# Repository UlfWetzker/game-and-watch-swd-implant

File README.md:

# Game & Watch SWD-Implant

A small [DAP-Link](https://github.com/ARMmbed/DAPLink) SWD programmer/debugger that fits insight a Nintendo® Game & Watch™ 2020.

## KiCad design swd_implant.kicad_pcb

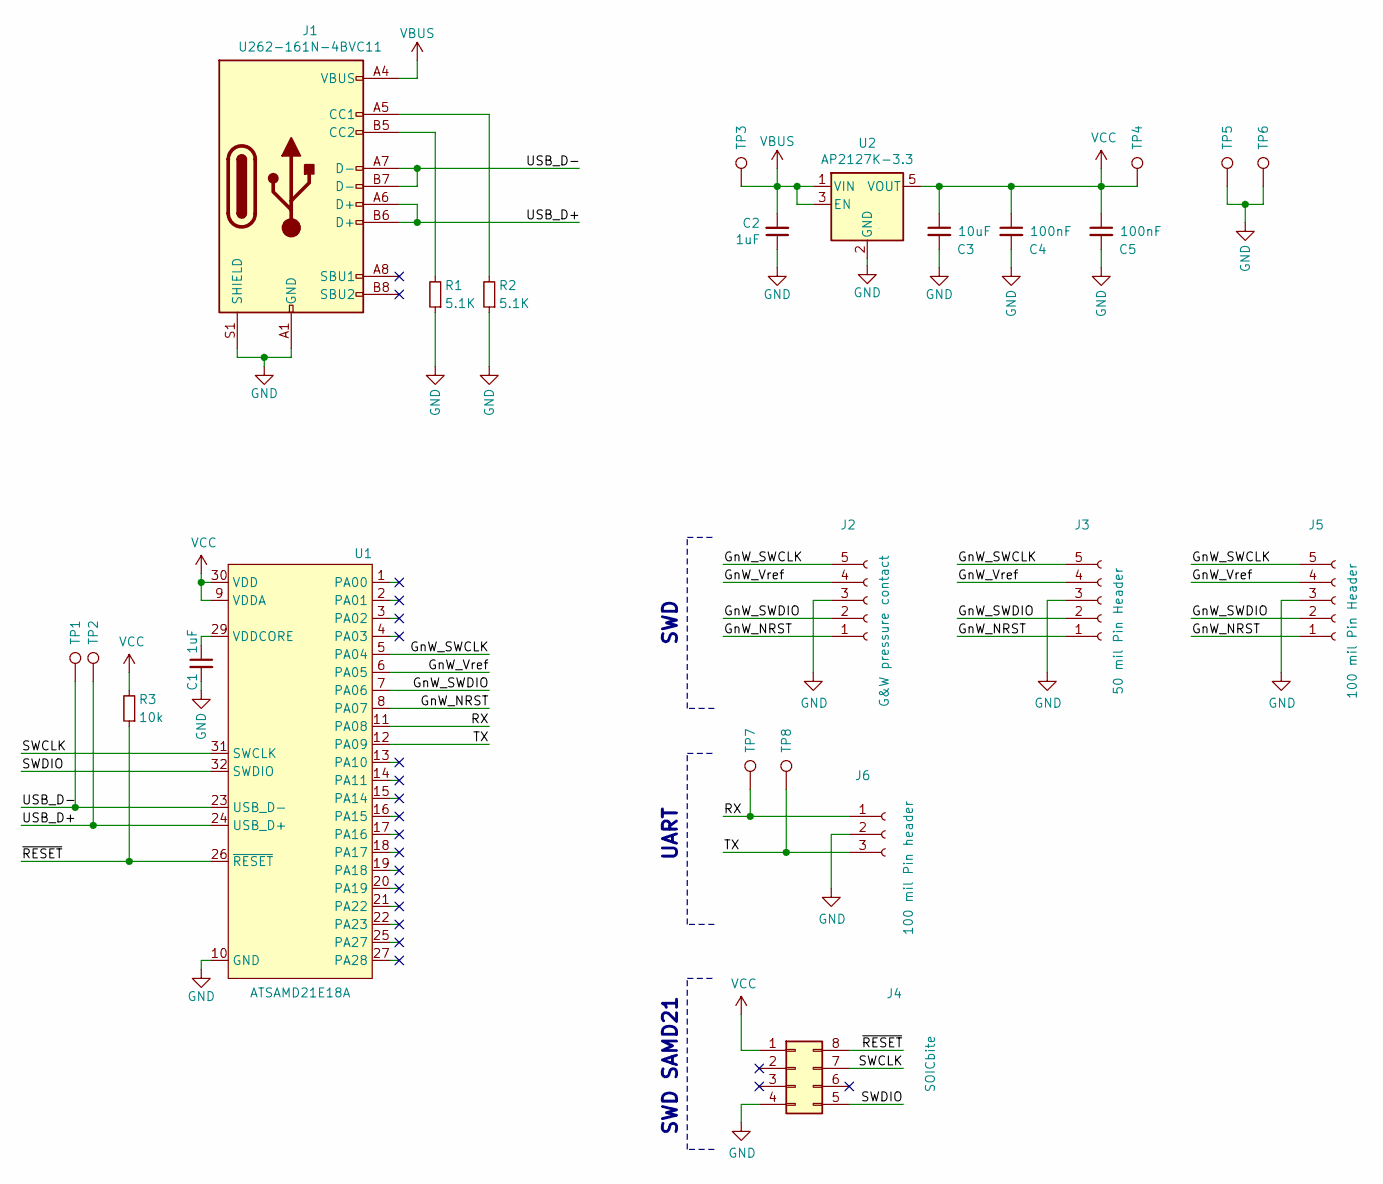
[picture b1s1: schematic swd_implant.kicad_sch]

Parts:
C1, C2: 1uF; C_0402_1005Metric; MFR.Part # CL05A105KA5NQNC; LCSC Part # C52923
C3: 10uF; C_0402_1005Metric; MFR.Part # CL05A106MQ5NUNC; LCSC Part # C15525
C4, C5: 100nF; C_0402_1005Metric; MFR.Part # CL05B104KO5NNNC; LCSC Part # C1525
J1: U262-161N-4BVC11; USB_C_Receptacle_XKB_U262-16XN-4BVC11; Mfr.Part # U262-161N-4BVC11; LCSC Part # C319148
J2: G&W pressure contact; GnW_SWD
J3: 50 mil Pin Header; PinHeader_1x05_P1.27mm_Vertical
J4: SOICbite; SOIC_clipProgSmall
J5: 100 mil Pin Header; PinHeader_1x05_P2.45mm_edge
J6: 100 mil Pin header; PinHeader_1x03_P2.45mm_edge
R1, R2: 5.1K; R_0402_1005Metric; MFR.Part # 0402WGF5101TCE; LCSC Part # C25905
R3: 10k; R_0402_1005Metric; MFR.Part # 0402WGJ0103TCE; LCSC Part # C25531
TP1, TP3, TP4, TP5, TP6, TP7, TP8: TP_USB_D+; TestPoint_Pad_D1.0mm
TP2: TP_USB_D-; TestPoint_Pad_D1.0mm
U1: ATSAMD21E18A; QFN-32-1EP_5x5mm_P0.5mm_EP3.6x3.6mm; MFR.Part # ATSAMD21E18A-MU; LCSC Part # C220692
U2: AP2127K-3.3; SOT-23-5; MFR.Part # AP2127K-3.3TRG1; LCSC Part # C156285

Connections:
/GnW_NRST: J2.1, J3.1, J5.1, U1.8 (PA07)
/GnW_SWCLK: J2.5, J3.5, J5.5, U1.5 (PA04)
/GnW_SWDIO: J2.2, J3.2, J5.2, U1.7 (PA06)
/GnW_Vref: J2.4, J3.4, J5.4, U1.6 (PA05)
/RX: J6.1, TP7.1, U1.11 (PA08)
/SWCLK: J4.7, U1.31 (SWCLK)
/SWDIO: J4.5, U1.32 (SWDIO)
/TX: J6.3, TP8.1, U1.12 (PA09)
/USB_D+: J1.A6 (D+), J1.B6 (D+), TP2.1, U1.24 (USB_D+)
/USB_D-: J1.A7 (D-), J1.B7 (D-), TP1.1, U1.23 (USB_D-)
/~RESET~: J4.8, R3.1, U1.26 (~RESET~)
GND: C1.2, C2.1, C3.2, C4.2, C5.2, J1.A1 (GND), J1.A12 (GND), J1.B1 (GND), J1.B12 (GND), J1.S1 (SHIELD), J2.3, J2.6, J2.7, J3.3, J4.4, J5.3, J6.2, R1.1, R2.1, TP5.1, TP6.1, U1.10 (GND), U1.28 (GND), U1.33, U2.2 (GND); also elsewhere on the board
unnamed: C1.1, U1.29 (VDDCORE)
unnamed: J1.A5 (CC1), R2.2
unnamed: J1.B5 (CC2), R1.2
VBUS: C2.2, J1.A4 (VBUS), J1.A9 (VBUS), J1.B4 (VBUS), J1.B9 (VBUS), TP3.1, U2.1 (VIN), U2.3 (EN)
VCC: C3.1, C4.1, C5.1, J4.1, R3.2, TP4.1, U1.9 (VDDA), U1.30 (VDD), U2.5 (VOUT)
no_connect_18: J1.A8 (SBU1)
no_connect_19: J1.B8 (SBU2)
no_connect_20: J4.2
no_connect_21: J4.3
no_connect_22: J4.6
no_connect_23: U1.1 (PA00)
no_connect_24: U1.13 (PA10)
no_connect_25: U1.14 (PA11)
no_connect_26: U1.15 (PA14)
no_connect_27: U1.16 (PA15)
no_connect_28: U1.17 (PA16)
no_connect_29: U1.18 (PA17)
no_connect_30: U1.19 (PA18)
no_connect_31: U1.2 (PA01)
no_connect_32: U1.20 (PA19)
no_connect_33: U1.21 (PA22)
no_connect_34: U1.22 (PA23)
no_connect_35: U1.25 (PA27)
no_connect_36: U1.27 (PA28)
no_connect_37: U1.3 (PA02)
no_connect_38: U1.4 (PA03)

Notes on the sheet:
SWD
UART
SWD SAMD21

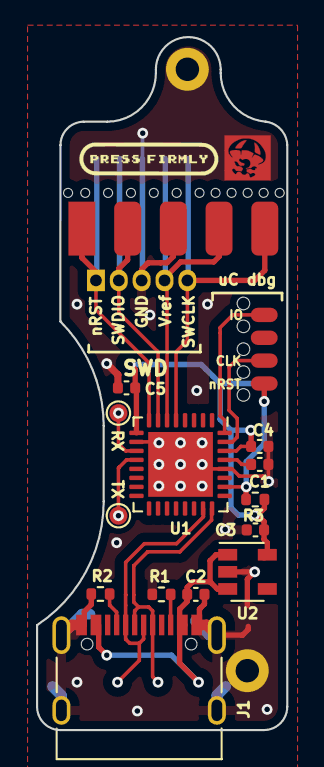
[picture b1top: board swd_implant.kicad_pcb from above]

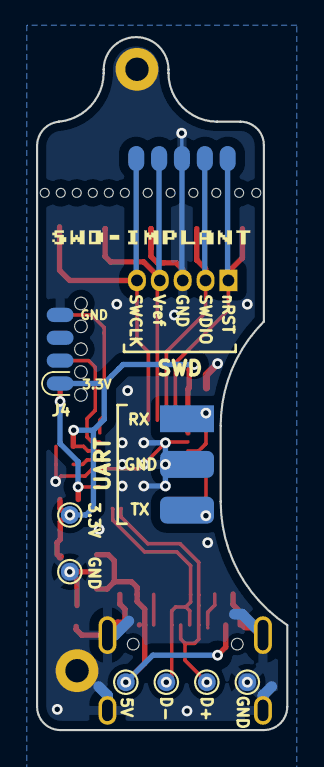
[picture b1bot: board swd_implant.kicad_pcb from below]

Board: 2 copper layers, 13.9 x 38.5 mm, 28 parts (10 on the bottom side), 17 nets.

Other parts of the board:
Ref**: Val**; MrGnW_Logo
Ref**#2: Val**; Press_firmly_Logo
Ref**#3: Val**; Wulf_Logo
Ref**#4: Val**; name_logo

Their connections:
GND: Ref**.1, Ref**.2, Ref**.3; also elsewhere on the board

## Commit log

2020-12-25 ignore backups
2020-12-25 Started readme
2020-12-29 Added a nicer symbol for the atsamd21
2020-12-29 Update on 50mil header to improve solderability
2020-12-29 Added a test point with a smaller silk ring
2020-12-29 Shorted by 0.5mm; thinner preasure contacts
2020-12-29 Changed board name
2020-12-29 Added 10k reset pullup
2020-12-29 0.5mm shorter; added test points for UART
2020-12-29 Update of project
2020-12-29 Update on images
